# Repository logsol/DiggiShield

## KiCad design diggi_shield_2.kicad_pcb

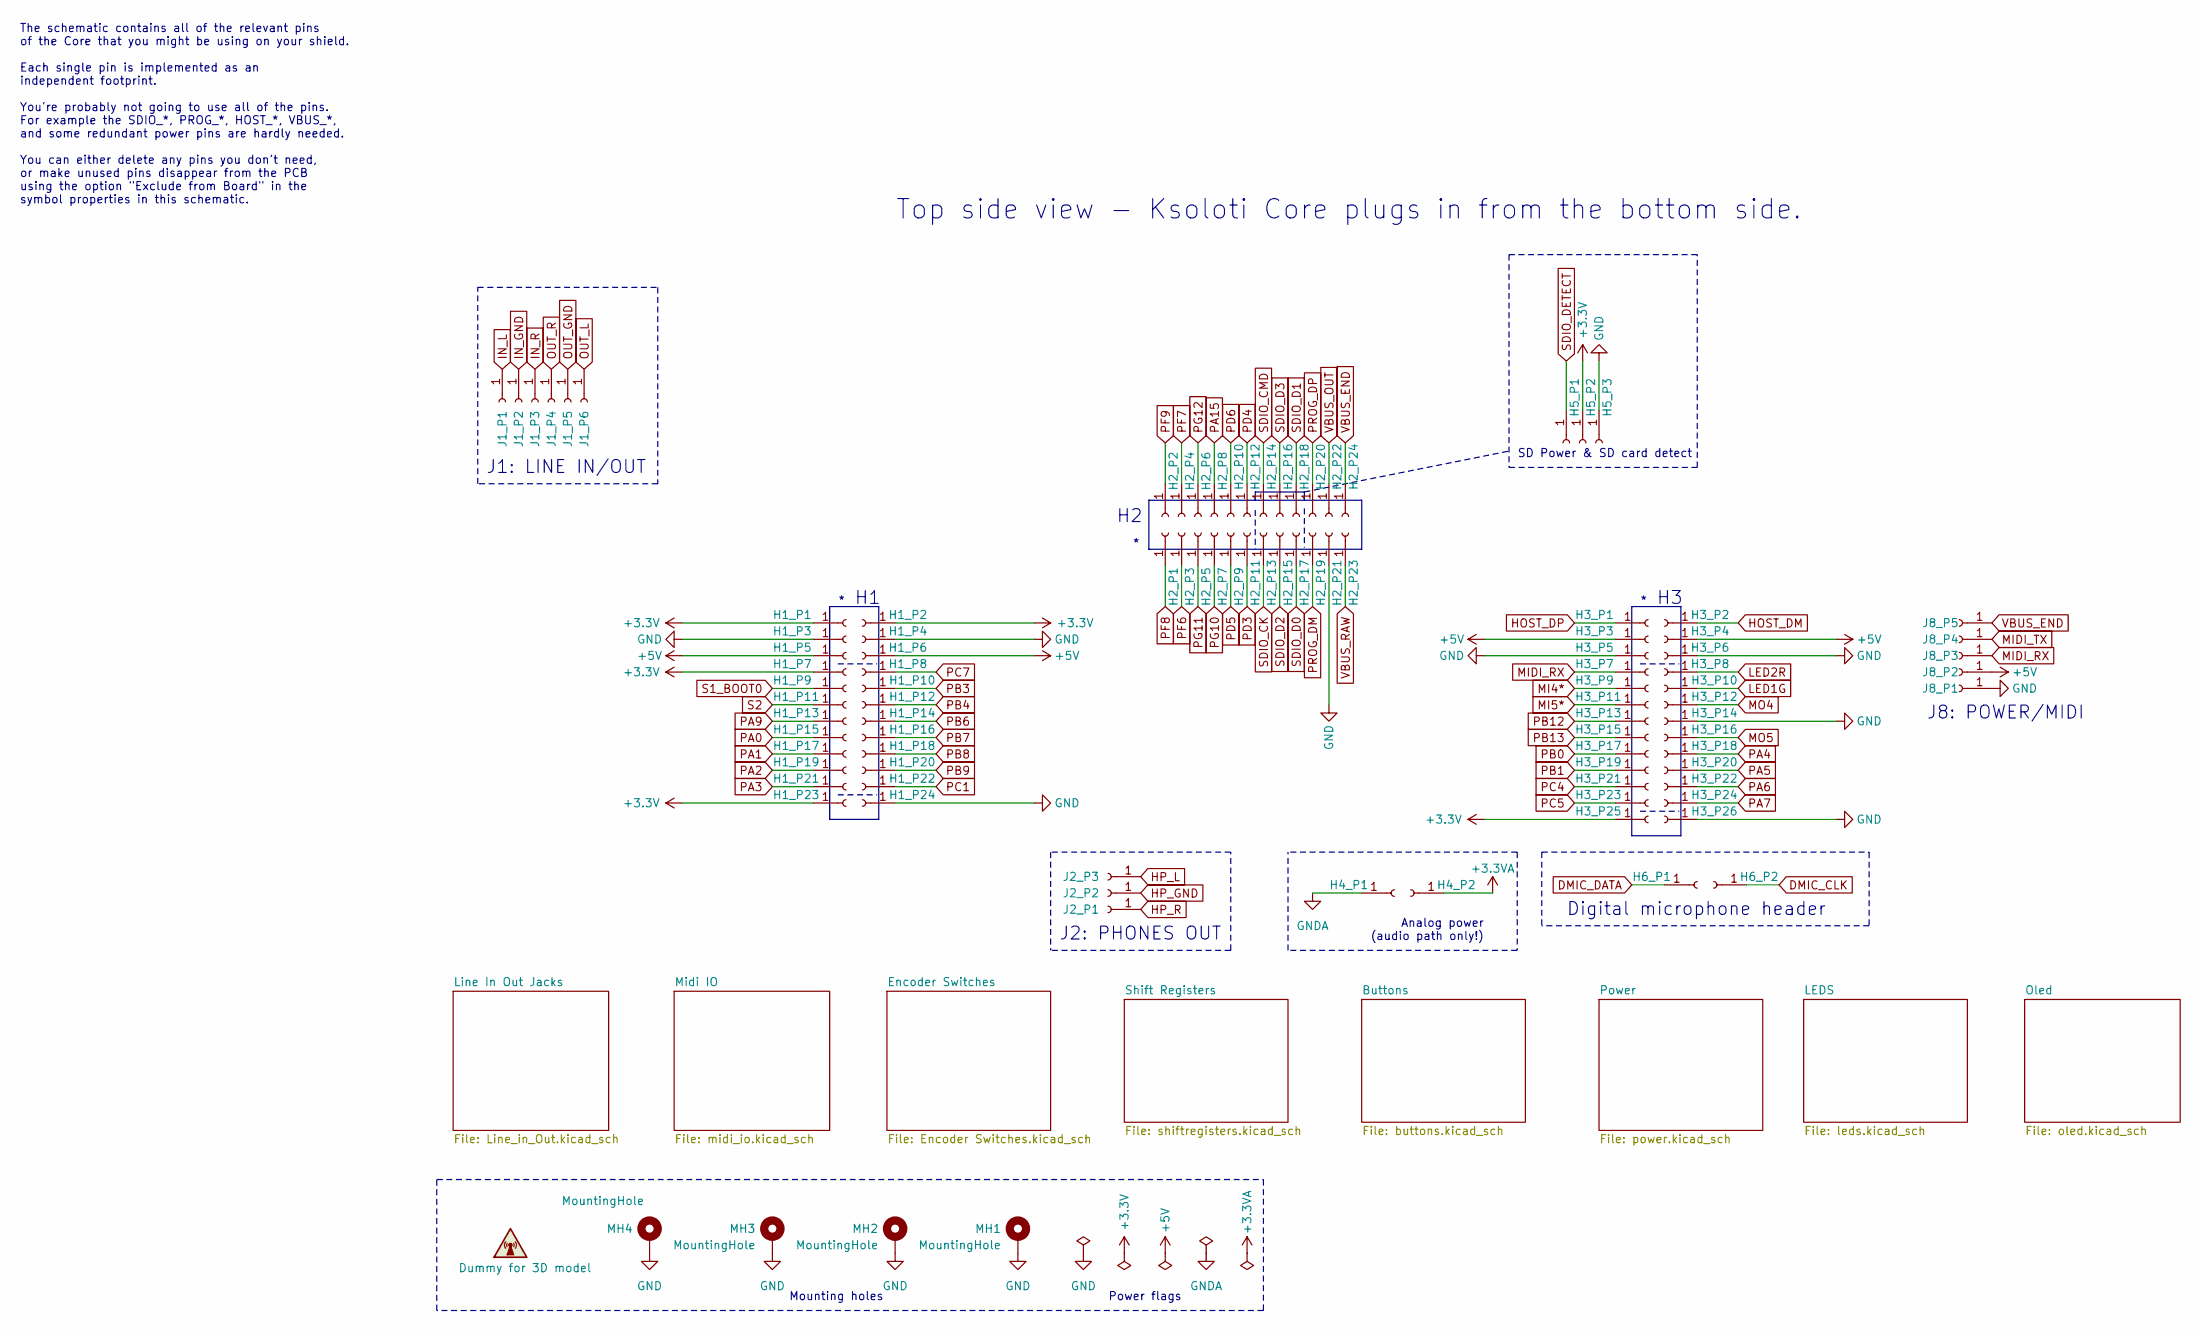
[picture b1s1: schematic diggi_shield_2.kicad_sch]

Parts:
DUMMY1: Dummy for 3D model
H1_P1: +3.3V; PinSocket_1x01_P2.54mm_Vertical_smcrt_sqr
H1_P2, H1_P7, H1_P23, H3_P25, H5_P2: +3.3V; PinSocket_1x01_P2.54mm_Vertical_smcrt_round
H1_P3, H1_P4, H1_P24, H2_P21, H3_P5, H3_P6, H3_P14, H3_P26, H5_P3: GND; PinSocket_1x01_P2.54mm_Vertical_smcrt_round
H1_P5, H1_P6, H3_P3, H3_P4: +5V; PinSocket_1x01_P2.54mm_Vertical_smcrt_round
H1_P8: PC7; PinSocket_1x01_P2.54mm_Vertical_smcrt_round
H1_P9: S1_BOOT0; PinSocket_1x01_P2.54mm_Vertical_smcrt_round
H1_P10: PB3; PinSocket_1x01_P2.54mm_Vertical_smcrt_round
H1_P11: S2; PinSocket_1x01_P2.54mm_Vertical_smcrt_round
H1_P12: PB4; PinSocket_1x01_P2.54mm_Vertical_smcrt_round
H1_P13: PA9; PinSocket_1x01_P2.54mm_Vertical_smcrt_round
H1_P14: PB6; PinSocket_1x01_P2.54mm_Vertical_smcrt_round
H1_P15: PA0; PinSocket_1x01_P2.54mm_Vertical_smcrt_round
H1_P16: PB7; PinSocket_1x01_P2.54mm_Vertical_smcrt_round
H1_P17: PA1; PinSocket_1x01_P2.54mm_Vertical_smcrt_round
H1_P18: PB8; PinSocket_1x01_P2.54mm_Vertical_smcrt_round
H1_P19: PA2; PinSocket_1x01_P2.54mm_Vertical_smcrt_round
H1_P20: PB9; PinSocket_1x01_P2.54mm_Vertical_smcrt_round
H1_P21: PA3; PinSocket_1x01_P2.54mm_Vertical_smcrt_round
H1_P22: PC1; PinSocket_1x01_P2.54mm_Vertical_smcrt_round
H2_P1: PF8; PinSocket_1x01_P2.54mm_Vertical_smcrt_sqr
H2_P2: PF9; PinSocket_1x01_P2.54mm_Vertical_smcrt_round
H2_P3: PF6; PinSocket_1x01_P2.54mm_Vertical_smcrt_round
H2_P4: PF7; PinSocket_1x01_P2.54mm_Vertical_smcrt_round
H2_P5: PG11; PinSocket_1x01_P2.54mm_Vertical_smcrt_round
H2_P6: PG12; PinSocket_1x01_P2.54mm_Vertical_smcrt_round
H2_P7: PG10; PinSocket_1x01_P2.54mm_Vertical_smcrt_round
H2_P8: PA15; PinSocket_1x01_P2.54mm_Vertical_smcrt_round
H2_P9: PD5; PinSocket_1x01_P2.54mm_Vertical_smcrt_round
H2_P10: PD6; PinSocket_1x01_P2.54mm_Vertical_smcrt_round
H2_P11: PD3; PinSocket_1x01_P2.54mm_Vertical_smcrt_round
H2_P12: PD4; PinSocket_1x01_P2.54mm_Vertical_smcrt_round
H2_P13: SDIO_CK; PinSocket_1x01_P2.54mm_Vertical_smcrt_round
H2_P14: SDIO_CMD; PinSocket_1x01_P2.54mm_Vertical_smcrt_round
H2_P15: SDIO_D2; PinSocket_1x01_P2.54mm_Vertical_smcrt_round
H2_P16: SDIO_D3; PinSocket_1x01_P2.54mm_Vertical_smcrt_round
H2_P17: SDIO_D0; PinSocket_1x01_P2.54mm_Vertical_smcrt_round
H2_P18: SDIO_D1; PinSocket_1x01_P2.54mm_Vertical_smcrt_round
H2_P19: PROG_DM; PinSocket_1x01_P2.54mm_Vertical_smcrt_round
H2_P20: PROG_DP; PinSocket_1x01_P2.54mm_Vertical_smcrt_round
H2_P22: VBUS_OUT; PinSocket_1x01_P2.54mm_Vertical_smcrt_round
H2_P23: VBUS_RAW; PinSocket_1x01_P2.54mm_Vertical_smcrt_round
H2_P24: VBUS_END; PinSocket_1x01_P2.54mm_Vertical_smcrt_round
H3_P1: HOST_DP; PinSocket_1x01_P2.54mm_Vertical_smcrt_sqr
H3_P2: HOST_DM; PinSocket_1x01_P2.54mm_Vertical_smcrt_round
H3_P7: MIDI_RX; PinSocket_1x01_P2.54mm_Vertical_smcrt_round
H3_P8: LED2R; PinSocket_1x01_P2.54mm_Vertical_smcrt_round
H3_P9: MI4; PinSocket_1x01_P2.54mm_Vertical_smcrt_round
H3_P10: LED1G; PinSocket_1x01_P2.54mm_Vertical_smcrt_round
H3_P11: MI5; PinSocket_1x01_P2.54mm_Vertical_smcrt_round
H3_P12: MO4; PinSocket_1x01_P2.54mm_Vertical_smcrt_round
H3_P13: PB12; PinSocket_1x01_P2.54mm_Vertical_smcrt_round
H3_P15: PB13; PinSocket_1x01_P2.54mm_Vertical_smcrt_round
H3_P16: MO5; PinSocket_1x01_P2.54mm_Vertical_smcrt_round
H3_P17: PB0; PinSocket_1x01_P2.54mm_Vertical_smcrt_round
H3_P18: PA4; PinSocket_1x01_P2.54mm_Vertical_smcrt_round
H3_P19: PB1; PinSocket_1x01_P2.54mm_Vertical_smcrt_round
H3_P20: PA5; PinSocket_1x01_P2.54mm_Vertical_smcrt_round
H3_P21: PC4; PinSocket_1x01_P2.54mm_Vertical_smcrt_round
H3_P22: PA6; PinSocket_1x01_P2.54mm_Vertical_smcrt_round
H3_P23: PC5; PinSocket_1x01_P2.54mm_Vertical_smcrt_round
H3_P24: PA7; PinSocket_1x01_P2.54mm_Vertical_smcrt_round
H4_P1: GNDA; PinSocket_1x01_P2.54mm_Vertical_smcrt_sqr
H4_P2: +3.3VA; PinSocket_1x01_P2.54mm_Vertical_smcrt_round
H5_P1: SDIO_DETECT; PinSocket_1x01_P2.54mm_Vertical_smcrt_sqr
H6_P1: DMIC_DATA; PinSocket_1x01_P2.54mm_Vertical_smcrt_round
H6_P2: DMIC_CLK; PinSocket_1x01_P2.54mm_Vertical_smcrt_round
J1_P1: IN_L; PinSocket_1x01_P2.54mm_Vertical_smcrt_sqr
J1_P2: IN_GND; PinSocket_1x01_P2.54mm_Vertical_smcrt_round
J1_P3: IN_R; PinSocket_1x01_P2.54mm_Vertical_smcrt_round
J1_P4: OUT_R; PinSocket_1x01_P2.54mm_Vertical_smcrt_round
J1_P5: OUT_GND; PinSocket_1x01_P2.54mm_Vertical_smcrt_round
J1_P6: OUT_L; PinSocket_1x01_P2.54mm_Vertical_smcrt_round
J2_P1: HP_R; PinSocket_1x01_P2.54mm_Vertical_smcrt_sqr
J2_P2: HP_GND; PinSocket_1x01_P2.54mm_Vertical_smcrt_round
J2_P3: HP_L; PinSocket_1x01_P2.54mm_Vertical_smcrt_round
J8_P1: GND; PinSocket_1x01_P2.54mm_Vertical_smcrt_sqr
J8_P2: +5V; PinSocket_1x01_P2.54mm_Vertical_smcrt_round
J8_P3: MIDI_RX*; PinSocket_1x01_P2.54mm_Vertical_smcrt_round
J8_P4: MIDI_TX; PinSocket_1x01_P2.54mm_Vertical_smcrt_round
J8_P5: VBUS_END; PinSocket_1x01_P2.54mm_Vertical_smcrt_round
MH1, MH2, MH3, MH4: MountingHole; MountingHole_3.2mm_M3_Pad_Via_tight

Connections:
+3.3V: H1_P1.1, H1_P2.1, H1_P7.1, H1_P23.1, H3_P25.1, H5_P2.1; also elsewhere on the board
+3.3VA: H4_P2.1
+5V: H1_P5.1, H1_P6.1, H3_P3.1, H3_P4.1, J8_P2.1; also elsewhere on the board
DMIC_CLK: H6_P2.1
DMIC_DATA: H6_P1.1
GND: H1_P3.1, H1_P4.1, H1_P24.1, H2_P21.1, H3_P5.1, H3_P6.1, H3_P14.1, H3_P26.1, H5_P3.1, J8_P1.1, MH1.1, MH2.1, MH3.1, MH4.1; also elsewhere on the board
GNDA: H4_P1.1
HOST_DM: H3_P2.1
HOST_DP: H3_P1.1
HP_GND: J2_P2.1; also elsewhere on the board
HP_L: J2_P3.1; also elsewhere on the board
HP_R: J2_P1.1; also elsewhere on the board
IN_GND: J1_P2.1; also elsewhere on the board
IN_L: J1_P1.1; also elsewhere on the board
IN_R: J1_P3.1; also elsewhere on the board
LED1G: H3_P10.1; also elsewhere on the board
LED2R: H3_P8.1; also elsewhere on the board
MI4*: H3_P9.1
MI5*: H3_P11.1
MIDI_RX: H3_P7.1, J8_P3.1; also elsewhere on the board
MIDI_TX: J8_P4.1
MO4: H3_P12.1; also elsewhere on the board
MO5: H3_P16.1; also elsewhere on the board
OUT_GND: J1_P5.1; also elsewhere on the board
OUT_L: J1_P6.1; also elsewhere on the board
OUT_R: J1_P4.1; also elsewhere on the board
PA0: H1_P15.1
PA1: H1_P17.1
PA2: H1_P19.1
PA3: H1_P21.1
PA4: H3_P18.1; also elsewhere on the board
PA5: H3_P20.1; also elsewhere on the board
PA6: H3_P22.1; also elsewhere on the board
PA7: H3_P24.1
PA9: H1_P13.1
PA15: H2_P8.1
PB0: H3_P17.1
PB1: H3_P19.1
PB3: H1_P10.1
PB4: H1_P12.1
PB6: H1_P14.1
PB7: H1_P16.1
PB8: H1_P18.1; also elsewhere on the board
PB9: H1_P20.1; also elsewhere on the board
PB12: H3_P13.1
PB13: H3_P15.1
PC1: H1_P22.1
PC4: H3_P21.1
PC5: H3_P23.1
PC7: H1_P8.1
PD3: H2_P11.1
PD4: H2_P12.1
PD5: H2_P9.1
PD6: H2_P10.1
PF6: H2_P3.1
PF7: H2_P4.1
PF8: H2_P1.1
PF9: H2_P2.1
PG10: H2_P7.1
PG11: H2_P5.1
PG12: H2_P6.1
PROG_DM: H2_P19.1
PROG_DP: H2_P20.1
S1_BOOT0: H1_P9.1
S2: H1_P11.1
SDIO_CK: H2_P13.1
SDIO_CMD: H2_P14.1
SDIO_D0: H2_P17.1
SDIO_D1: H2_P18.1
SDIO_D2: H2_P15.1
SDIO_D3: H2_P16.1
SDIO_DETECT: H5_P1.1
VBUS_END: H2_P24.1, J8_P5.1; also elsewhere on the board
VBUS_OUT: H2_P22.1
VBUS_RAW: H2_P23.1

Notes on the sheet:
J2: PHONES OUT
The schematic contains all of the relevant pins of the Core that you might be using on your shield. Each single pin is implemented as an independent footprint. You're probably not going to use all of the pins. For example the SDIO_*, PROG_*, HOST_*, VBUS_*, and some redundant power pins are hardly 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
J8: POWER/MIDI
Mounting holes
Top side view - Ksoloti Core plugs in from the bottom side.
Power flags
SD Power & SD card detect
Analog power (audio path only!)
J1: LINE IN/OUT
Digital microphone header

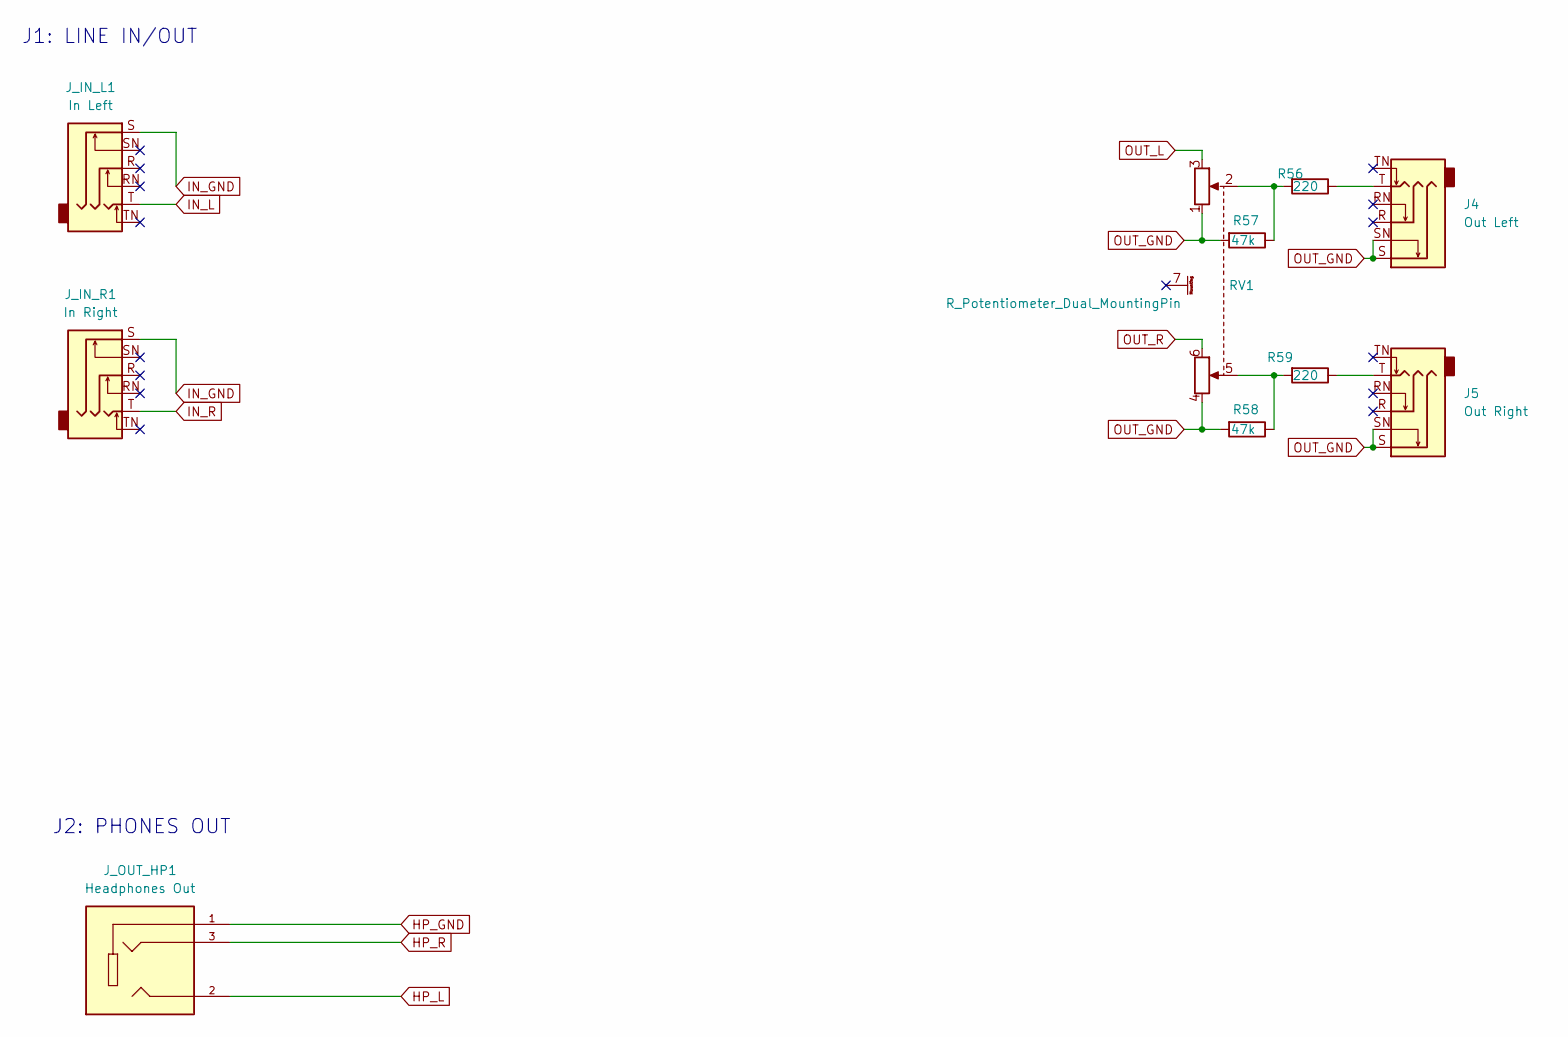
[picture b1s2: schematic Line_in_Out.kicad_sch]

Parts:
J4: Out Left; Jack_6.35mm_Neutrik_NRJ6HF_Horizontal_no_screwhole
J5: Out Right; Jack_6.35mm_Neutrik_NRJ6HF_Horizontal_no_screwhole
J_IN_L1: In Left; Jack_6.35mm_Neutrik_NRJ6HF_Horizontal_no_screwhole
J_IN_R1: In Right; Jack_6.35mm_Neutrik_NRJ6HF_Horizontal_no_screwhole
J_OUT_HP1: Headphones Out; CUI_SJ1-3523N; PARTREV 1.05
R56, R59: 220; R_0603_1608Metric
R57, R58: 47k; R_0603_1608Metric
RV1: R_Potentiometer_Dual_MountingPin; ALPS_POT_VERTICAL_PS_DUAL

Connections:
HP_GND: J_OUT_HP1.S; also elsewhere on the board
HP_L: J_OUT_HP1.T; also elsewhere on the board
HP_R: J_OUT_HP1.R; also elsewhere on the board
IN_GND: J_IN_L1.S, J_IN_R1.S; also elsewhere on the board
IN_L: J_IN_L1.T; also elsewhere on the board
IN_R: J_IN_R1.T; also elsewhere on the board
unnamed: J4.T, R56.1
unnamed: J5.T, R59.1
unnamed: R56.2, R57.1, RV1.2
unnamed: R58.1, R59.2, RV1.5
OUT_GND: J4.S, J4.SN, J5.S, J5.SN, R57.2, R58.2, RV1.1, RV1.4; also elsewhere on the board
OUT_L: RV1.3; also elsewhere on the board
OUT_R: RV1.6; also elsewhere on the board

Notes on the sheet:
J2: PHONES OUT
J1: LINE IN/OUT

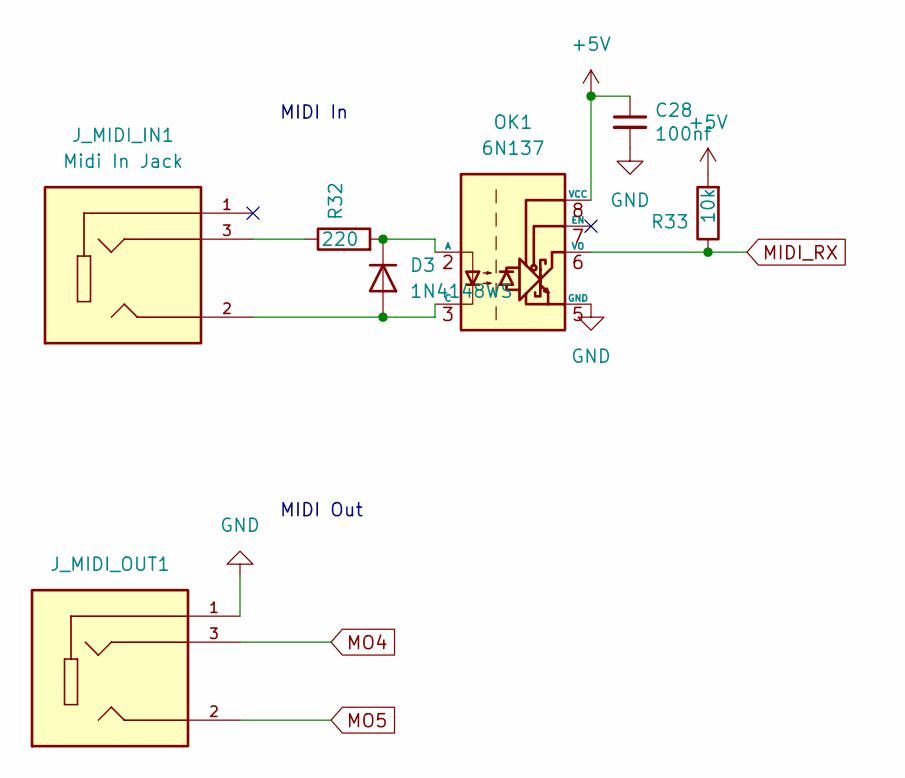
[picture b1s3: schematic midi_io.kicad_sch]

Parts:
C28: 100nf; C_0603_1608Metric
D3: 1N4148WS; D_SOD-323
J_MIDI_IN1: Midi In Jack; CUI_SJ1-3523N; PARTREV 1.05
J_MIDI_OUT1: Midi Out Jack; CUI_SJ1-3523N; PARTREV 1.05
OK1: 6N137; SMDIP-8_W9.53mm
R32: 220; R_0603_1608Metric
R33: 10k; R_0603_1608Metric

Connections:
+5V: C28.1, OK1.8 (VCC), R33.2; also elsewhere on the board
GND: C28.2, J_MIDI_OUT1.1, J_MIDI_OUT1.S, OK1.5 (GND); also elsewhere on the board
MIDI_RX: OK1.6 (VO), R33.1; also elsewhere on the board
MO4: J_MIDI_OUT1.R; also elsewhere on the board
MO5: J_MIDI_OUT1.T; also elsewhere on the board
unnamed: D3.2 (A), J_MIDI_IN1.2, J_MIDI_IN1.T, OK1.3 (C)
unnamed: D3.1 (K), OK1.2 (A), R32.2
unnamed: J_MIDI_IN1.3, J_MIDI_IN1.R, R32.1

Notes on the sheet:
MIDI Out
MIDI In

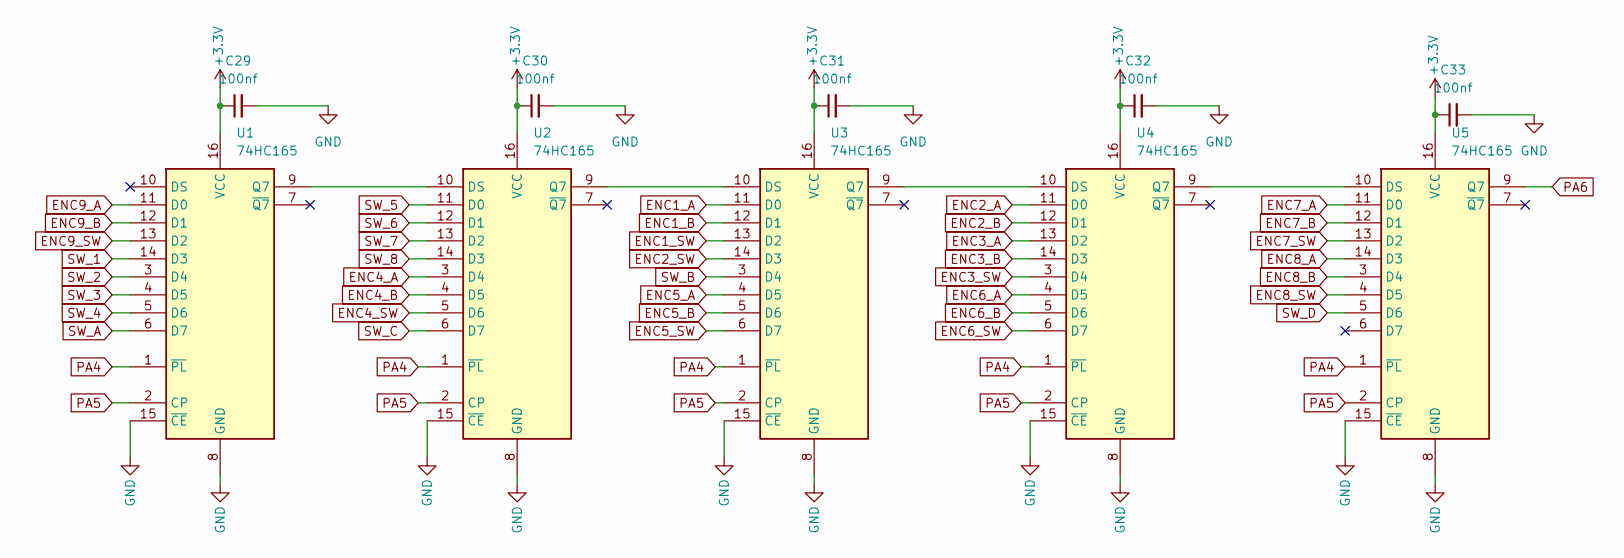
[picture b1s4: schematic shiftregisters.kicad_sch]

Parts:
C29, C30, C31, C32, C33: 100nf; C_0603_1608Metric
U1, U2, U3, U4, U5: 74HC165; SOP65P640X120-16

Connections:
+3.3V: C29.1, C30.1, C31.1, C32.1, C33.1, U1.16 (VCC), U2.16 (VCC), U3.16 (VCC), U4.16 (VCC), U5.16 (VCC); also elsewhere on the board
ENC1_A: U3.11 (D0); also elsewhere on the board
ENC1_B: U3.12 (D1); also elsewhere on the board
ENC1_SW: U3.13 (D2); also elsewhere on the board
ENC2_A: U4.11 (D0); also elsewhere on the board
ENC2_B: U4.12 (D1); also elsewhere on the board
ENC2_SW: U3.14 (D3); also elsewhere on the board
ENC3_A: U4.13 (D2); also elsewhere on the board
ENC3_B: U4.14 (D3); also elsewhere on the board
ENC3_SW: U4.3 (D4); also elsewhere on the board
ENC4_A: U2.3 (D4); also elsewhere on the board
ENC4_B: U2.4 (D5); also elsewhere on the board
ENC4_SW: U2.5 (D6); also elsewhere on the board
ENC5_A: U3.4 (D5); also elsewhere on the board
ENC5_B: U3.5 (D6); also elsewhere on the board
ENC5_SW: U3.6 (D7); also elsewhere on the board
ENC6_A: U4.4 (D5); also elsewhere on the board
ENC6_B: U4.5 (D6); also elsewhere on the board
ENC6_SW: U4.6 (D7); also elsewhere on the board
ENC7_A: U5.11 (D0); also elsewhere on the board
ENC7_B: U5.12 (D1); also elsewhere on the board
ENC7_SW: U5.13 (D2); also elsewhere on the board
ENC8_A: U5.14 (D3); also elsewhere on the board
ENC8_B: U5.3 (D4); also elsewhere on the board
ENC8_SW: U5.4 (D5); also elsewhere on the board
ENC9_A: U1.11 (D0); also elsewhere on the board
ENC9_B: U1.12 (D1); also elsewhere on the board
ENC9_SW: U1.13 (D2); also elsewhere on the board
GND: C29.2, C30.2, C31.2, C32.2, C33.2, U1.8 (GND), U1.15 (~CE), U2.8 (GND), U2.15 (~CE), U3.8 (GND), U3.15 (~CE), U4.8 (GND), U4.15 (~CE), U5.8 (GND), U5.15 (~CE); also elsewhere on the board
unnamed: U1.9 (Q7), U2.10 (DS)
unnamed: U2.9 (Q7), U3.10 (DS)
unnamed: U3.9 (Q7), U4.10 (DS)
unnamed: U4.9 (Q7), U5.10 (DS)
PA4: U1.1 (~PL), U2.1 (~PL), U3.1 (~PL), U4.1 (~PL), U5.1 (~PL); also elsewhere on the board
PA5: U1.2 (CP), U2.2 (CP), U3.2 (CP), U4.2 (CP), U5.2 (CP); also elsewhere on the board
PA6: U5.9 (Q7); also elsewhere on the board
SW_1: U1.14 (D3); also elsewhere on the board
SW_2: U1.3 (D4); also elsewhere on the board
SW_3: U1.4 (D5); also elsewhere on the board
SW_4: U1.5 (D6); also elsewhere on the board
SW_5: U2.11 (D0); also elsewhere on the board
SW_6: U2.12 (D1); also elsewhere on the board
SW_7: U2.13 (D2); also elsewhere on the board
SW_8: U2.14 (D3); also elsewhere on the board
SW_A: U1.6 (D7); also elsewhere on the board
SW_B: U3.3 (D4); also elsewhere on the board
SW_C: U2.6 (D7); also elsewhere on the board
SW_D: U5.5 (D6); also elsewhere on the board

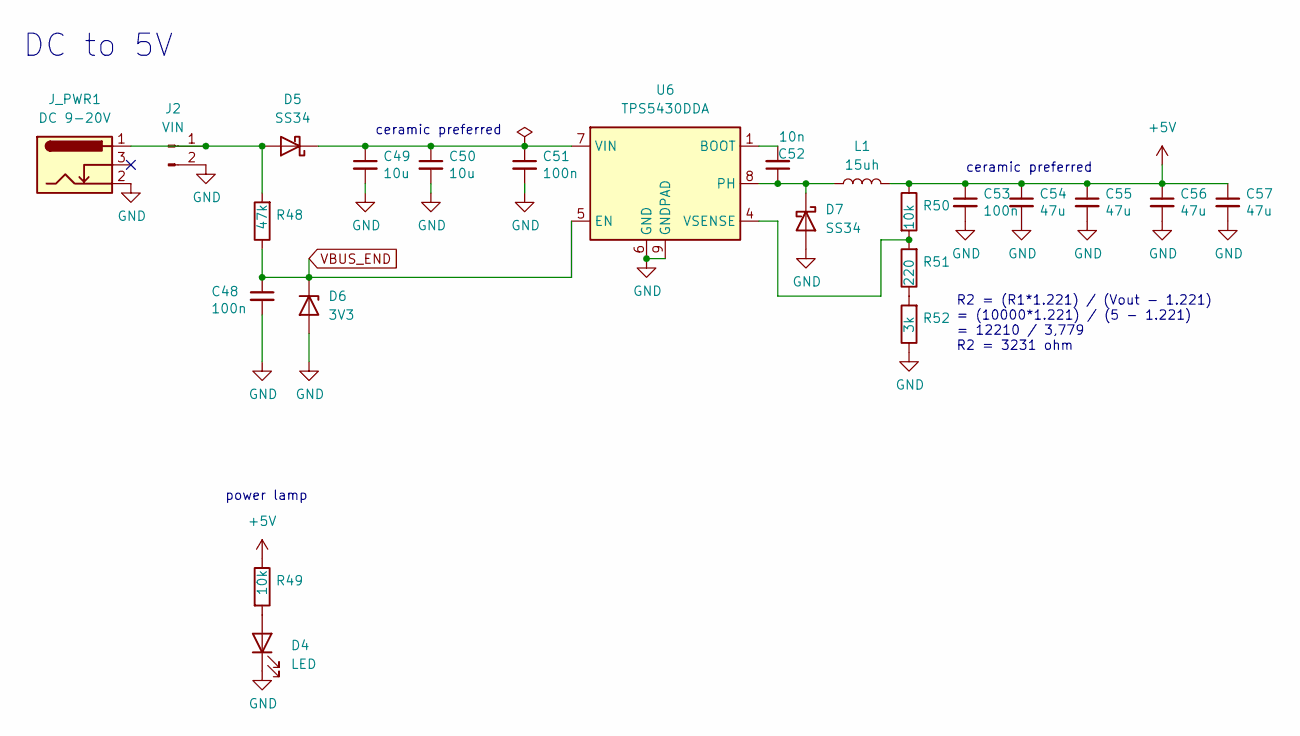
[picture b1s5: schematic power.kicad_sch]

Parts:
C48, C51, C53: 100n; C_0603_1608Metric
C49, C50: 10u; C_0603_1608Metric
C52: 10n; C_0603_1608Metric
C54, C55, C56, C57: 47u; C_1206_3216Metric
D4: LED; LED_0603_1608Metric
D5, D7: SS34; D_SMA
D6: 3V3; D_MiniMELF
J2: VIN; PinHeader_1x02_P2.54mm_Vertical
J_PWR1: DC 9-20V; BarrelJack_GCT_DCJ200-10-A_Horizontal
L1: 15uh; L_10.4x10.4_H4.8
R48: 47k; R_0603_1608Metric
R49, R50: 10k; R_0603_1608Metric
R51: 220; R_0603_1608Metric
R52: 3k; R_0603_1608Metric
U6: TPS5430DDA; TI_SO-PowerPAD-8_ThermalVias

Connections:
+5V: C53.1, C54.1, C55.1, C56.1, C57.1, L1.2, R49.1, R50.1; also elsewhere on the board
GND: C48.2, C49.2, C50.2, C51.2, C53.2, C54.2, C55.2, C56.2, C57.2, D4.1 (K), D6.2 (A), D7.2 (A), J2.2, J_PWR1.2, R52.1, U6.6 (GND), U6.9 (GNDPAD); also elsewhere on the board
unnamed: D4.2 (A), R49.2
unnamed: D5.2 (A), J2.1, J_PWR1.1, R48.2
unnamed: C49.1, C50.1, C51.1, D5.1 (K), U6.7 (VIN)
unnamed: C52.1, D7.1 (K), L1.1, U6.8 (PH)
unnamed: R51.1, R52.2
unnamed: C52.2, U6.1 (BOOT)
unnamed: R50.2, R51.2, U6.4 (VSENSE)
VBUS_END: C48.1, D6.1 (K), R48.1, U6.5 (EN); also elsewhere on the board

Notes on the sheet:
R2 = (R1*1.221) / (Vout - 1.221) = (10000*1.221) / (5 - 1.221) = 12210 / 3,779 R2 = 3231 ohm
power lamp
ceramic preferred
DC to 5V

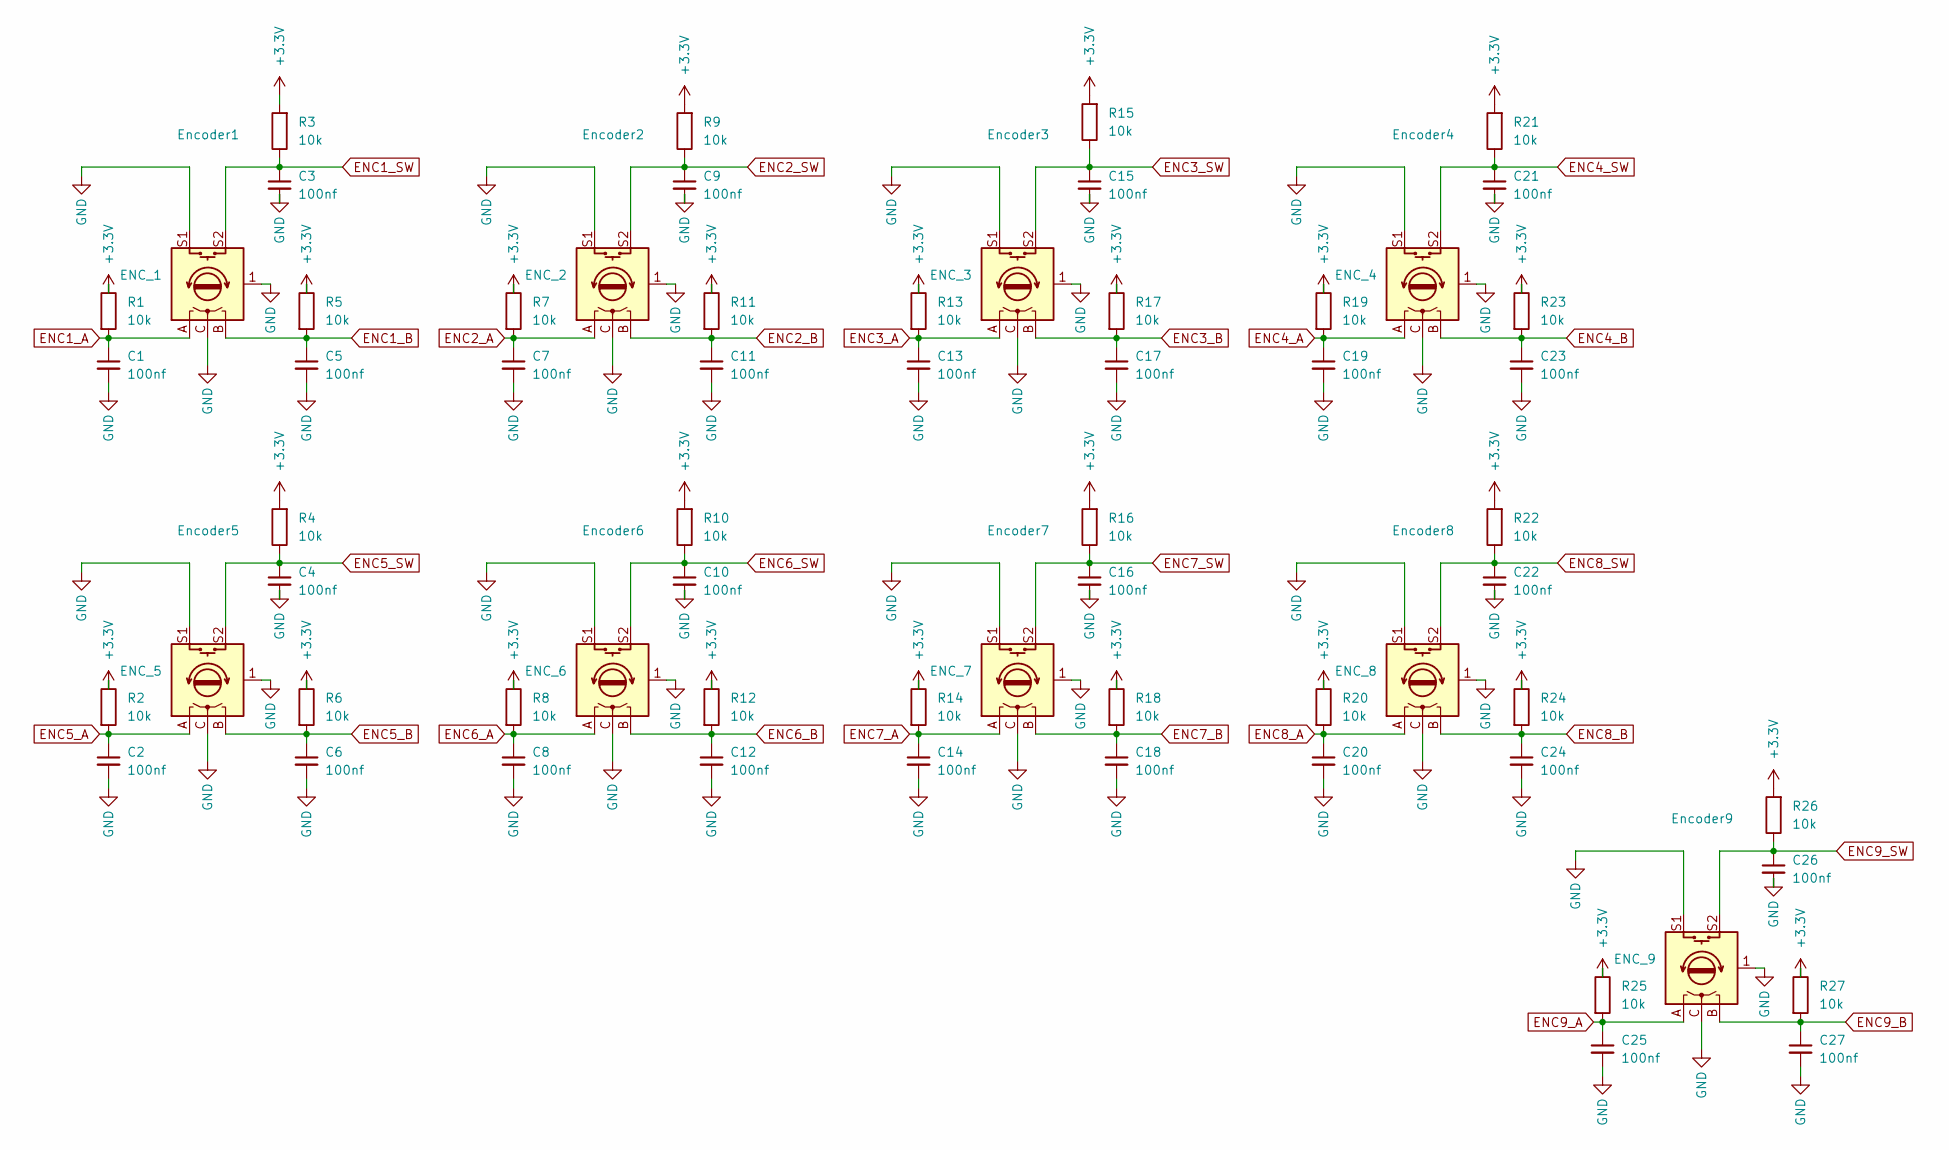
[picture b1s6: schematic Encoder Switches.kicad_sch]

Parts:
C1, C2, C3, C4, C5, C6, C7, C8, C9, C10, C11, C12, C13, C14, C15, C16, C17, C18, C19, C20, C21, C22, C23, C24, C25, C26, C27: 100nf; C_0603_1608Metric
ENC_1: Encoder1; ALPS_STEC12E08
ENC_2: Encoder2; ALPS_STEC12E08
ENC_3: Encoder3; ALPS_STEC12E08
ENC_4: Encoder4; ALPS_STEC12E08
ENC_5: Encoder5; ALPS_STEC12E08
ENC_6: Encoder6; ALPS_STEC12E08
ENC_7: Encoder7; ALPS_STEC12E08
ENC_8: Encoder8; ALPS_STEC12E08
ENC_9: Encoder9; ALPS_STEC12E08
R1, R2, R3, R4, R5, R6, R7, R8, R9, R10, R11, R12, R13, R14, R15, R16, R17, R18, R19, R20, R21, R22, R23, R24, R25, R26, R27: 10k; R_0201_0603Metric

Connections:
+3.3V: R1.1, R2.1, R3.2, R4.2, R5.1, R6.1, R7.1, R8.1, R9.2, R10.2, R11.1, R12.1, R13.1, R14.1, R15.2, R16.2, R17.1, R18.1, R19.1, R20.1, R21.2, R22.2, R23.1, R24.1, R25.1, R26.2, R27.1; also elsewhere on the board
ENC1_A: C1.1, ENC_1.A, R1.2; also elsewhere on the board
ENC1_B: C5.1, ENC_1.B, R5.2; also elsewhere on the board
ENC1_SW: C3.1, ENC_1.S2, R3.1; also elsewhere on the board
ENC2_A: C7.1, ENC_2.A, R7.2; also elsewhere on the board
ENC2_B: C11.1, ENC_2.B, R11.2; also elsewhere on the board
ENC2_SW: C9.1, ENC_2.S2, R9.1; also elsewhere on the board
ENC3_A: C13.1, ENC_3.A, R13.2; also elsewhere on the board
ENC3_B: C17.1, ENC_3.B, R17.2; also elsewhere on the board
ENC3_SW: C15.1, ENC_3.S2, R15.1; also elsewhere on the board
ENC4_A: C19.1, ENC_4.A, R19.2; also elsewhere on the board
ENC4_B: C23.1, ENC_4.B, R23.2; also elsewhere on the board
ENC4_SW: C21.1, ENC_4.S2, R21.1; also elsewhere on the board
ENC5_A: C2.1, ENC_5.A, R2.2; also elsewhere on the board
ENC5_B: C6.1, ENC_5.B, R6.2; also elsewhere on the board
ENC5_SW: C4.1, ENC_5.S2, R4.1; also elsewhere on the board
ENC6_A: C8.1, ENC_6.A, R8.2; also elsewhere on the board
ENC6_B: C12.1, ENC_6.B, R12.2; also elsewhere on the board
ENC6_SW: C10.1, ENC_6.S2, R10.1; also elsewhere on the board
ENC7_A: C14.1, ENC_7.A, R14.2; also elsewhere on the board
ENC7_B: C18.1, ENC_7.B, R18.2; also elsewhere on the board
ENC7_SW: C16.1, ENC_7.S2, R16.1; also elsewhere on the board
ENC8_A: C20.1, ENC_8.A, R20.2; also elsewhere on the board
ENC8_B: C24.1, ENC_8.B, R24.2; also elsewhere on the board
ENC8_SW: C22.1, ENC_8.S2, R22.1; also elsewhere on the board
ENC9_A: C25.1, ENC_9.A, R25.2; also elsewhere on the board
ENC9_B: C27.1, ENC_9.B, R27.2; also elsewhere on the board
ENC9_SW: C26.1, ENC_9.S2, R26.1; also elsewhere on the board
GND: C1.2, C2.2, C3.2, C4.2, C5.2, C6.2, C7.2, C8.2, C9.2, C10.2, C11.2, C12.2, C13.2, C14.2, C15.2, C16.2, C17.2, C18.2, C19.2, C20.2, C21.2, C22.2, C23.2, C24.2, C25.2, C26.2, C27.2, ENC_1.1, ENC_1.C, ENC_1.S1, ENC_2.1, ENC_2.C, ENC_2.S1, ENC_3.1, ENC_3.C, ENC_3.S1, ENC_4.1, ENC_4.C, ENC_4.S1, ENC_5.1, ENC_5.C, ENC_5.S1, ENC_6.1, ENC_6.C, ENC_6.S1, ENC_7.1, ENC_7.C, ENC_7.S1, ENC_8.1, ENC_8.C, ENC_8.S1, ENC_9.1, ENC_9.C, ENC_9.S1; also elsewhere on the board

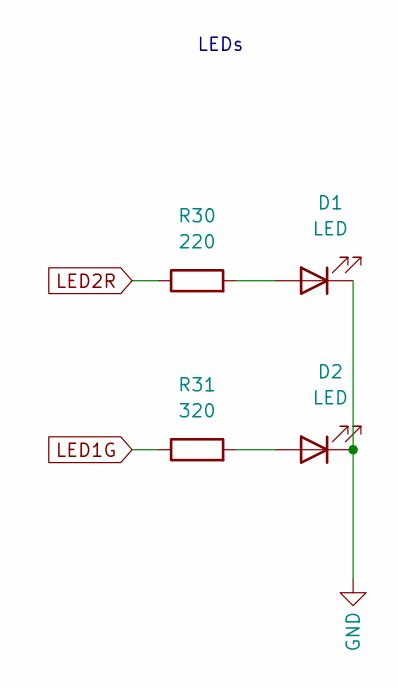
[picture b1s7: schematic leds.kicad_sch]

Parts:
D1, D2: LED; LED_D2.0mm_W4.0mm_H2.8mm_FlatTop
R30: 220; R_0201_0603Metric
R31: 320; R_0201_0603Metric

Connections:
GND: D1.1 (K), D2.1 (K); also elsewhere on the board
LED1G: R31.1; also elsewhere on the board
LED2R: R30.1; also elsewhere on the board
unnamed: D1.2 (A), R30.2
unnamed: D2.2 (A), R31.2

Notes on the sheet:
LEDs

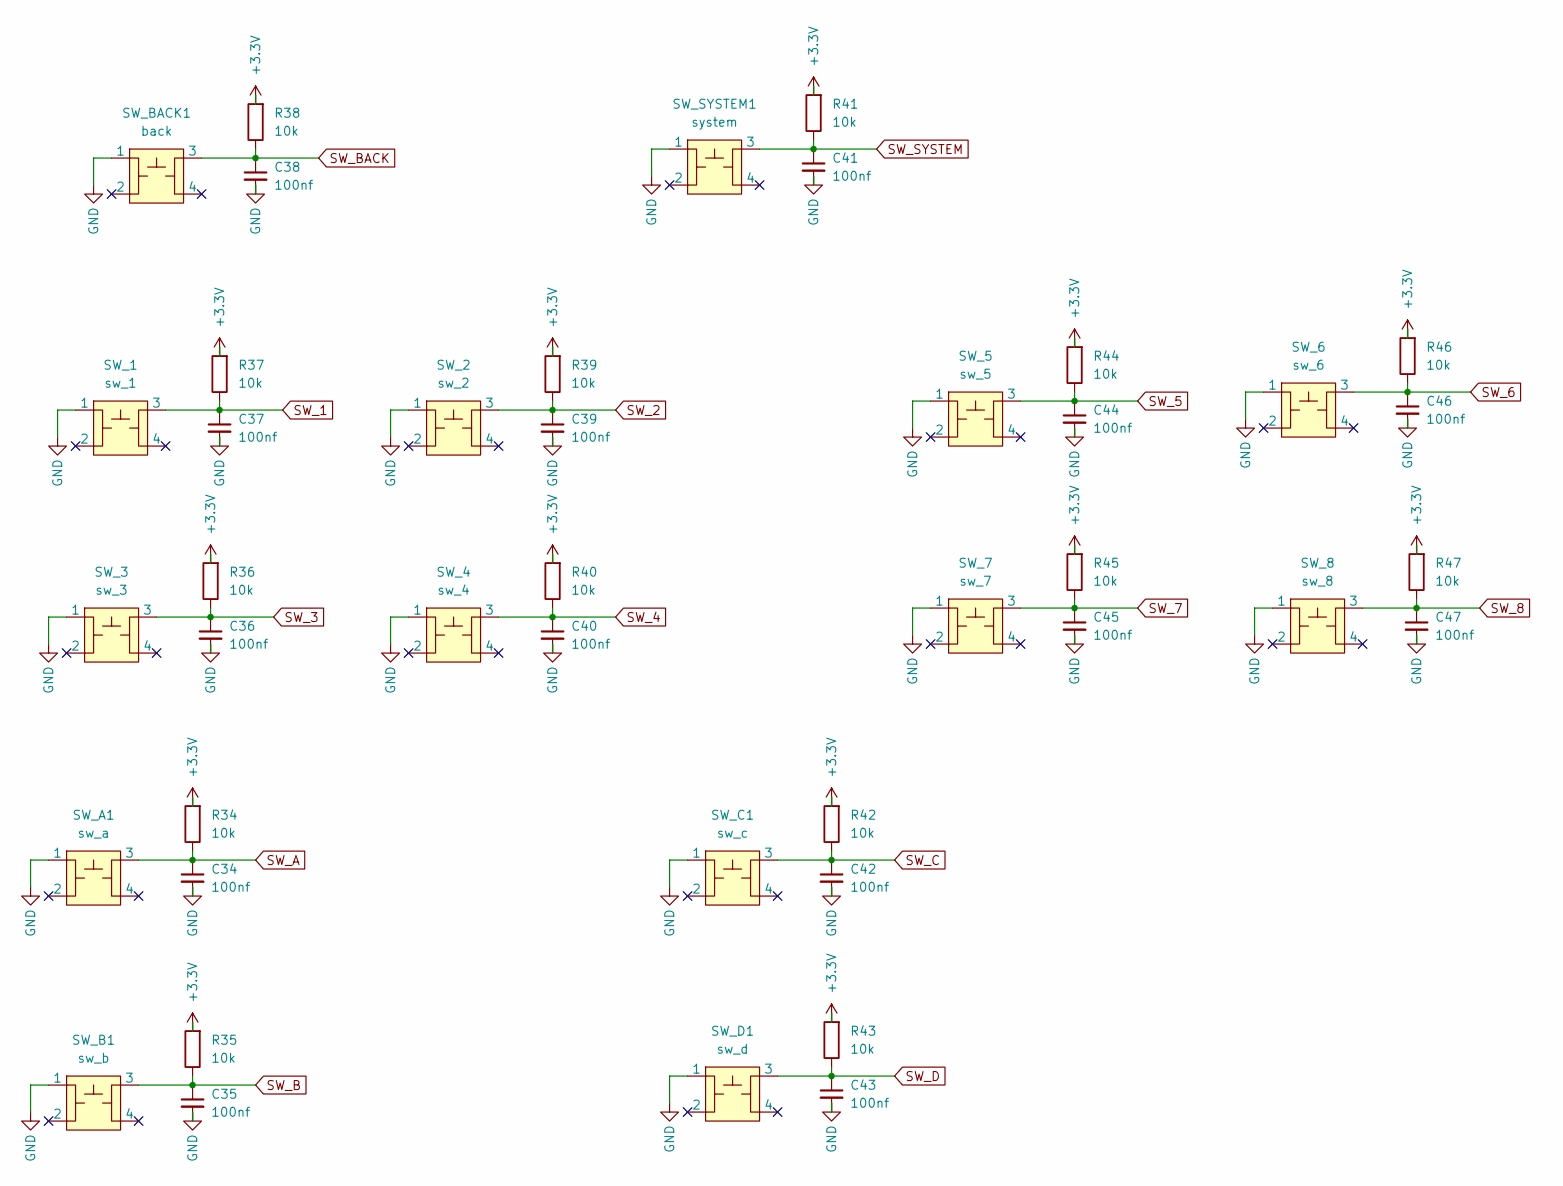
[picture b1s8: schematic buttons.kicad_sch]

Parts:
C34, C35, C36, C37, C38, C39, C40, C41, C42, C43, C44, C45, C46, C47: 100nf; C_0603_1608Metric
R34, R35, R36, R37, R38, R39, R40, R41, R42, R43, R44, R45, R46, R47: 10k; R_0201_0603Metric
SW_1: sw_1; TL1105T
SW_2: sw_2; TL1105T
SW_3: sw_3; TL1105T
SW_4: sw_4; TL1105T
SW_5: sw_5; TL1105T
SW_6: sw_6; TL1105T
SW_7: sw_7; TL1105T
SW_8: sw_8; TL1105T
SW_A1: sw_a; TL1105T
SW_B1: sw_b; TL1105T
SW_BACK1: back; TL1105T
SW_C1: sw_c; TL1105T
SW_D1: sw_d; TL1105T
SW_SYSTEM1: system; TL1105T

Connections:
+3.3V: R34.2, R35.2, R36.2, R37.2, R38.2, R39.2, R40.2, R41.2, R42.2, R43.2, R44.2, R45.2, R46.2, R47.2; also elsewhere on the board
GND: C34.2, C35.2, C36.2, C37.2, C38.2, C39.2, C40.2, C41.2, C42.2, C43.2, C44.2, C45.2, C46.2, C47.2, SW_1.1, SW_2.1, SW_3.1, SW_4.1, SW_5.1, SW_6.1, SW_7.1, SW_8.1, SW_A1.1, SW_B1.1, SW_BACK1.1, SW_C1.1, SW_D1.1, SW_SYSTEM1.1; also elsewhere on the board
SW_1: C37.1, R37.1, SW_1.3; also elsewhere on the board
SW_2: C39.1, R39.1, SW_2.3; also elsewhere on the board
SW_3: C36.1, R36.1, SW_3.3; also elsewhere on the board
SW_4: C40.1, R40.1, SW_4.3; also elsewhere on the board
SW_5: C44.1, R44.1, SW_5.3; also elsewhere on the board
SW_6: C46.1, R46.1, SW_6.3; also elsewhere on the board
SW_7: C45.1, R45.1, SW_7.3; also elsewhere on the board
SW_8: C47.1, R47.1, SW_8.3; also elsewhere on the board
SW_A: C34.1, R34.1, SW_A1.3; also elsewhere on the board
SW_B: C35.1, R35.1, SW_B1.3; also elsewhere on the board
SW_BACK: C38.1, R38.1, SW_BACK1.3
SW_C: C42.1, R42.1, SW_C1.3; also elsewhere on the board
SW_D: C43.1, R43.1, SW_D1.3; also elsewhere on the board
SW_SYSTEM: C41.1, R41.1, SW_SYSTEM1.3

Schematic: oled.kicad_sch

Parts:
J6: I2C_HEADER; PinHeader_1x04_P2.54mm_Vertical
OLED1: 128x64_OLED; 2.42 OLED Simon Karl Custom
R28, R29: 2.7k; R_0201_0603Metric

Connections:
+3.3V: R28.1, R29.1; also elsewhere on the board
+5V: J6.2, OLED1.2 (VIN); also elsewhere on the board
GND: J6.1, OLED1.1 (GND); also elsewhere on the board
PB8: J6.3, OLED1.3 (SCL), R29.2; also elsewhere on the board
PB9: J6.4, OLED1.4 (SDA), R28.2; also elsewhere on the board

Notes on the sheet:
OLED 1.3" 128x64 I2C SH1106

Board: 4 copper layers, 264 parts (101 on the bottom side), 84 nets, no tracks yet.

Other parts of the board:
G513513: LOGO

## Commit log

2025-04-02 Added oled hierarchical page and referenced other pages
2025-04-02 Fixed pcb and ran some electrical rule checking and fixed some issues mainly connections and power flags
2025-04-02 Adding line out circuitry based on gills schematic
2025-04-09 Annotated all components (numerating)
2025-04-11 Cleaned up ERC errors
2025-04-11 Get rid of some warnings
2025-04-11 Added dual poti edits to diggi symbol library
2025-04-11 Female to socket symbol
2025-04-11 Solve all warnings
2025-04-11 added OLED footprint and library
2025-04-11 Remove symbol copy warnings
2025-04-11 Removed final warnings
2025-04-16 Added jack symbols and footprints also footprints for ics and caps
